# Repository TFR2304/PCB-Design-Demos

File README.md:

# PCB-Design-Demos
Collection of projects that showcase basic/intermediate knowledge of different EDA softwares and PCB design rules

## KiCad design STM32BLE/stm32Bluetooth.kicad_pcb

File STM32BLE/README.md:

These files contain the schematic, pcb design and footprints created for this project, which involved the development of a STM32 based board with BLE capabilities.
This project was heavily influenced by the following online tutorial series: https://www.youtube.com/watch?v=nkHFoxe0mrU & https://www.youtube.com/watch?v=PlXd3lLZ4vc .

Thank you Phil!

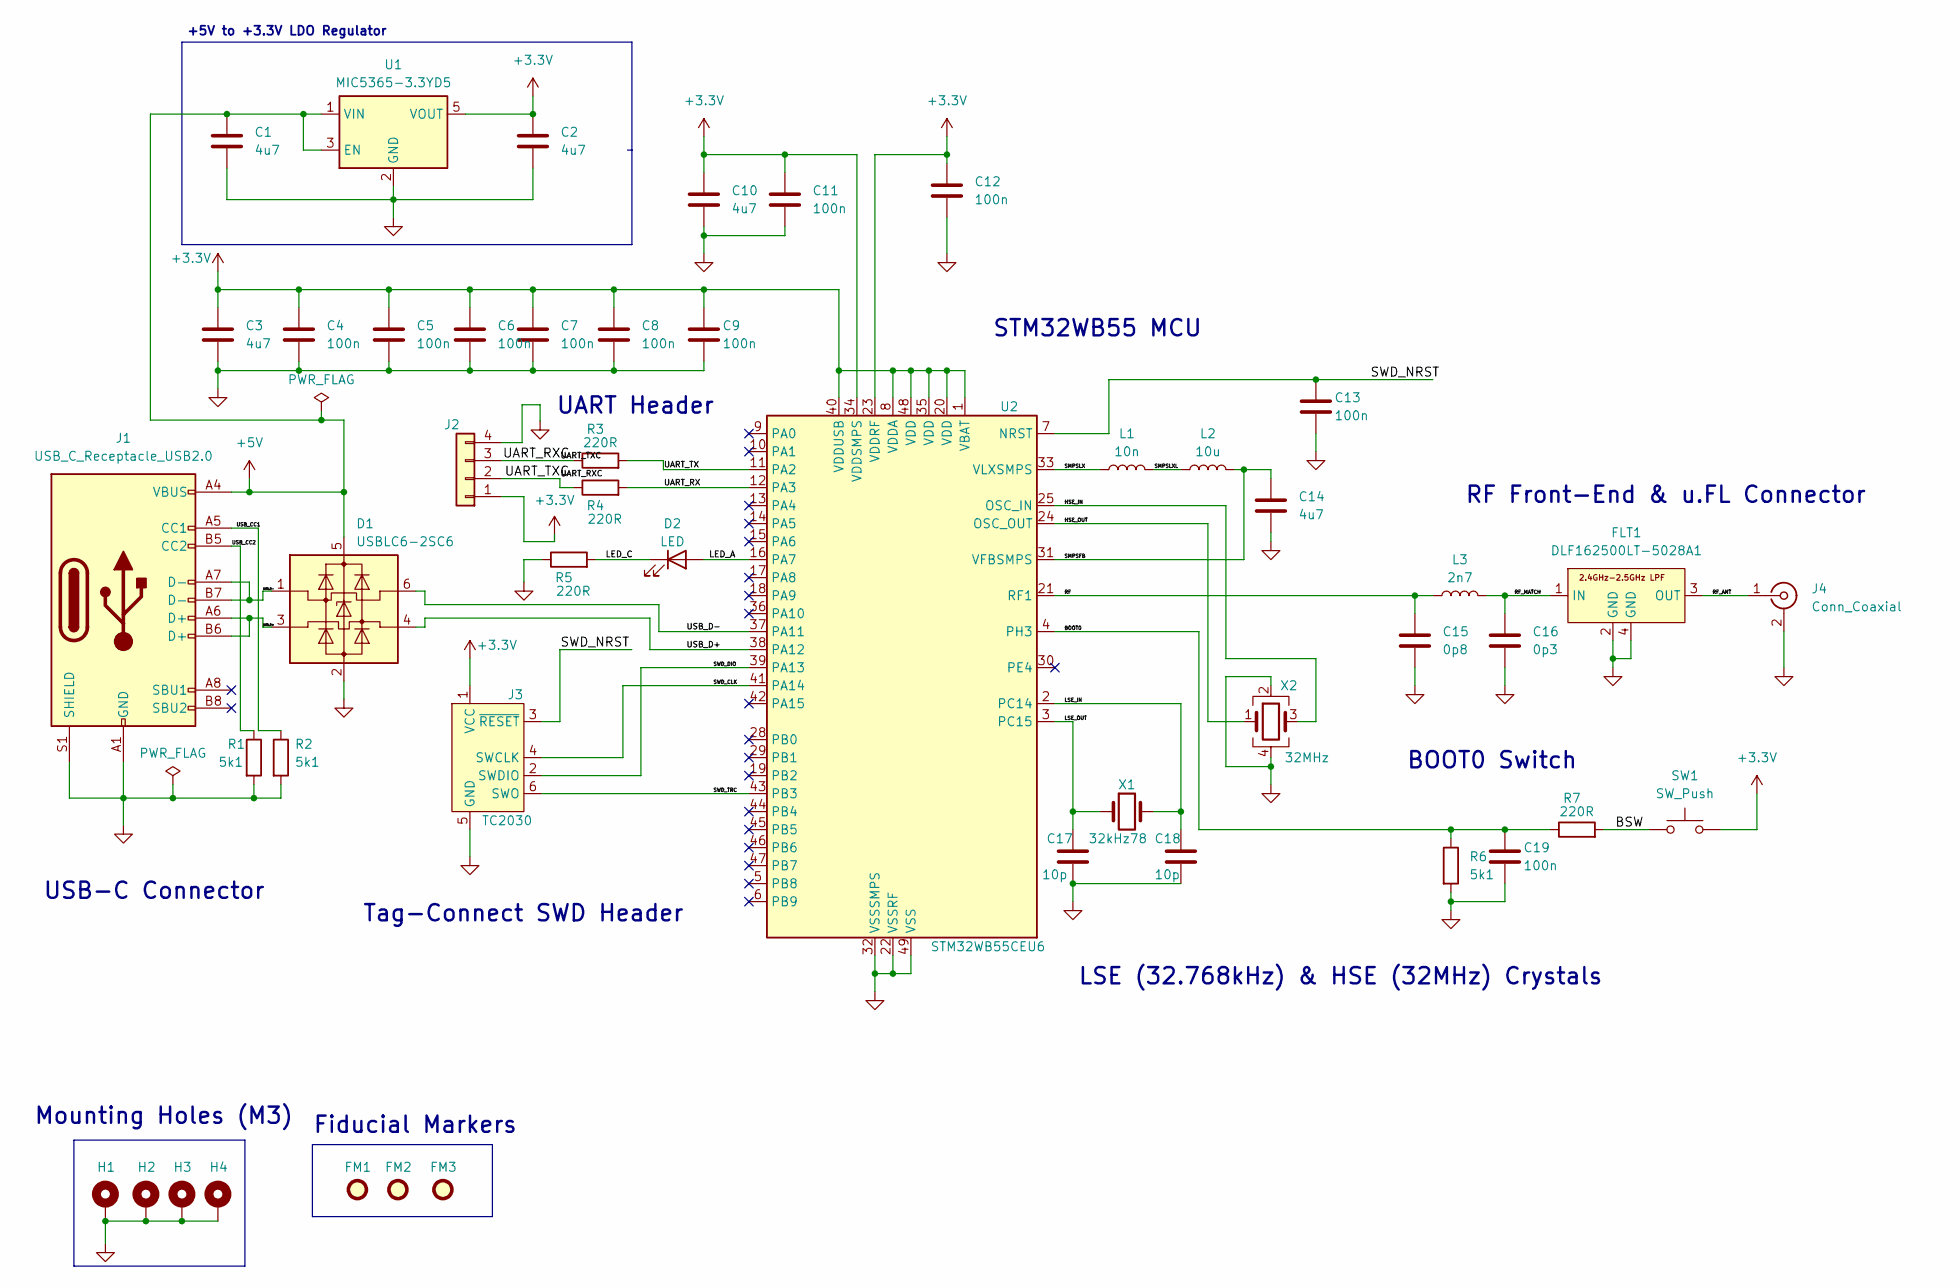
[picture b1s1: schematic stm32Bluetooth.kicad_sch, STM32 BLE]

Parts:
C1, C2, C3, C10, C14: 4u7; C_0603_1608Metric
C4, C5, C6, C7, C8, C9, C11, C12, C13, C19: 100n; C_0402_1005Metric
C15: 0p8; C_0402_1005Metric
C16: 0p3; C_0402_1005Metric
C17, C18: 10p; C_0402_1005Metric
D1: USBLC6-2SC6; SOT-23-6
D2: LED; LED_0402_1005Metric
FLT1: DLF162500LT-5028A1
FM1, FM2, FM3: Fiducial; Fiducial_1mm_Mask2mm
H1, H2, H3, H4: MountingHole_Pad; MountingHole_2.2mm_M2_Pad_Via
J1: USB_C_Receptacle_USB2.0; USB_C_Receptacle_GCT_USB4105-xx-A_16P_TopMnt_Horizontal
J2: Conn_01x04; Molex_PicoBlade_53048-0410_1x04_P1.25mm_Horizontal
J3: TC2030; Tag-Connect_TC2030-IDC-FP_2x03_P1.27mm_Vertical
J4: Conn_Coaxial; U.FL_Hirose_U.FL-R-SMT-1_Vertical
L1: 10n; L_0402_1005Metric
L2: 10u; L_0805_2012Metric
L3: 2n7; L_0402_1005Metric
R1, R2, R6: 5k1; R_0402_1005Metric
R3, R4, R5, R7: 220R; R_0402_1005Metric
SW1: SW_Push; SW_SPST_CK_RS282G05A3
U1: MIC5365-3.3YD5; SOT-23-5
U2: STM32WB55CEU6; QFN-48-1EP_7x7mm_P0.5mm_EP5.6x5.6mm
X1: 32kHz78; Crystal_SMD_2012-2Pin_2.0x1.2mm
X2: 32MHz; Crystal_SMD_2016-4Pin_2.0x1.6mm

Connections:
+3.3V: C2.1, C3.1, C4.1, C5.1, C6.1, C7.1, C8.1, C9.1, C10.1, C11.1, C12.1, J2.1, J3.1 (VCC), SW1.2, U1.5 (VOUT), U2.1 (VBAT), U2.8 (VDDA), U2.20 (VDD), U2.23 (VDDRF), U2.34 (VDDSMPS), U2.35 (VDD), U2.40 (VDDUSB), U2.48 (VDD)
+5V: C1.1, D1.5 (VBUS), J1.A4 (VBUS), J1.A9 (VBUS), J1.B4 (VBUS), J1.B9 (VBUS), U1.1 (VIN), U1.3 (EN)
/BOOT0: C19.1, R6.1, R7.1, U2.4 (PH3)
/BSW: R7.2, SW1.1
/HSE_IN: U2.25 (OSC_IN), X2.3
/HSE_OUT: U2.24 (OSC_OUT), X2.1
/LED_A: D2.2 (A), U2.16 (PA7)
/LED_C: D2.1 (K), R5.2
/LSE_IN: C18.1, U2.2 (PC14), X1.2
/LSE_OUT: C17.1, U2.3 (PC15), X1.1
/RF: C15.1, L3.1, U2.21 (RF1)
/RF_ANT: FLT1.3 (OUT), J4.1 (In)
/RF_MATCH: C16.1, FLT1.1 (IN), L3.2
/SMPSFB: C14.1, L2.2, U2.31 (VFBSMPS)
/SMPSLX: L1.1, U2.33 (VLXSMPS)
/SMPSLXL: L1.2, L2.1
/SWD_CLK: J3.4 (SWCLK), U2.41 (PA14)
/SWD_DIO: J3.2 (SWDIO), U2.39 (PA13)
/SWD_NRST: C13.1, J3.3 (~RESET), U2.7 (NRST)
/SWD_TRC: J3.6 (SWO), U2.43 (PB3)
/UART_RX: R4.2, U2.12 (PA3)
/UART_RXC: J2.2, J2.3, R3.1, R4.1
/UART_TX: R3.2, U2.11 (PA2)
/USB_CC1: J1.A5 (CC1), R2.1
/USB_CC2: J1.B5 (CC2), R1.1
/USB_D+: D1.3 (I/O1), D1.4 (I/O2), J1.A6 (D+), J1.B6 (D+), U2.38 (PA12)
/USB_D-: D1.1 (I/O1), D1.6 (I/O2), J1.A7 (D-), J1.B7 (D-), U2.37 (PA11)
GND: C1.2, C2.2, C3.2, C4.2, C5.2, C6.2, C7.2, C8.2, C9.2, C10.2, C11.2, C12.2, C13.2, C14.2, C15.2, C16.2, C17.2, C18.2, C19.2, D1.2 (GND), FLT1.2 (GND), FLT1.4 (GND), H1.1, H2.1, H3.1, H4.1, J1.A1 (GND), J1.A12 (GND), J1.B1 (GND), J1.B12 (GND), J1.S1 (SHIELD), J2.4, J3.5 (GND), J4.2 (Ext), R1.2, R2.2, R5.1, R6.2, U1.2 (GND), U2.22 (VSSRF), U2.32 (VSSSMPS), U2.49 (VSS), X2.2, X2.4

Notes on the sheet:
USB-C Connector
BOOT0 Switch
Tag-Connect SWD Header
RF Front-End & u.FL Connector
+5V to +3.3V LDO Regulator
Fiducial Markers
Mounting Holes (M3)
UART Header
LSE (32.768kHz) & HSE (32MHz) Crystals
STM32WB55 MCU

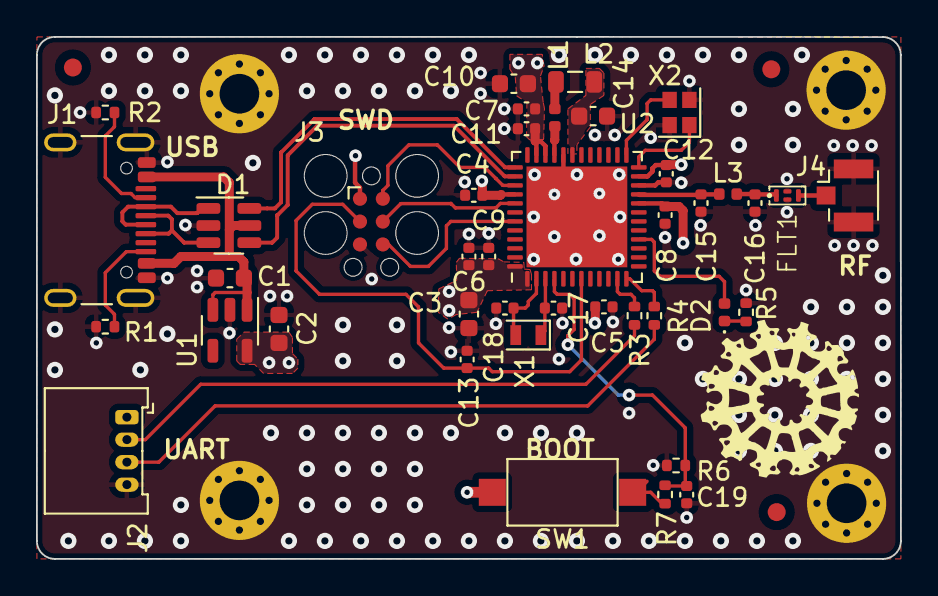
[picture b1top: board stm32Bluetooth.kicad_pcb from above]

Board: 4 copper layers, 48.0 x 29.0 mm, 48 parts (0 on the bottom side), 28 nets.

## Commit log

2024-07-16 Create demo
